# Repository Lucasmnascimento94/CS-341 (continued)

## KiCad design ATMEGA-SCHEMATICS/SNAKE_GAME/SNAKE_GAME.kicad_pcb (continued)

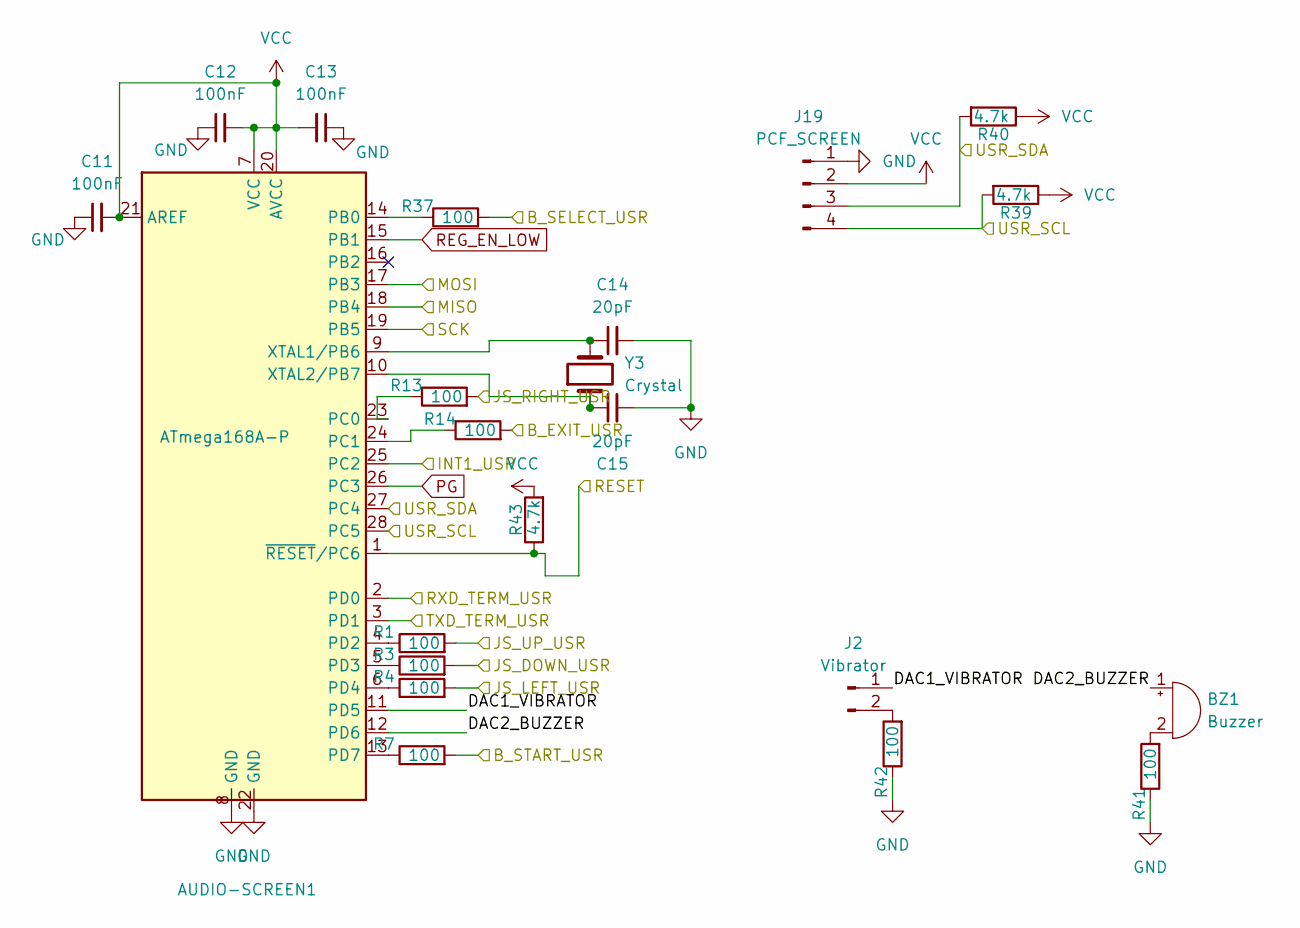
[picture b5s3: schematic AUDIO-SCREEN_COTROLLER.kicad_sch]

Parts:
AUDIO-SCREEN1: ATmega168A-P; DIP-28_W7.62mm
BZ1: Buzzer; Buzzer_12x9.5RM7.6
C11, C12, C13: 100nF; C_Disc_D7.5mm_W5.0mm_P5.00mm
C14, C15: 20pF; CP_Radial_D5.0mm_P2.50mm
J2: Vibrator; TerminalBlock_MaiXu_MX126-5.0-02P_1x02_P5.00mm
J19: PCF_SCREEN; TerminalBlock_MaiXu_MX126-5.0-04P_1x04_P5.00mm
R1, R3, R4, R7, R13, R14, R37, R41, R42: 100; R_Axial_DIN0207_L6.3mm_D2.5mm_P10.16mm_Horizontal
R39, R40, R43: 4.7k; R_Axial_DIN0207_L6.3mm_D2.5mm_P10.16mm_Horizontal
Y3: Crystal; Resonator-2Pin_W6.0mm_H3.0mm

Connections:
/AUDIO-SCREEN_CONTROLLER/B_EXIT_USR: R14.2; also elsewhere on the board
/AUDIO-SCREEN_CONTROLLER/B_SELECT_USR: R37.2; also elsewhere on the board
/AUDIO-SCREEN_CONTROLLER/B_START_USR: R7.2; also elsewhere on the board
/AUDIO-SCREEN_CONTROLLER/DAC1_VIBRATOR: AUDIO-SCREEN1.11 (PD5), J2.1
/AUDIO-SCREEN_CONTROLLER/DAC2_BUZZER: AUDIO-SCREEN1.12 (PD6), BZ1.1 (+)
/AUDIO-SCREEN_CONTROLLER/INT1_USR: AUDIO-SCREEN1.25 (PC2); also elsewhere on the board
/AUDIO-SCREEN_CONTROLLER/JS_DOWN_USR: R3.2; also elsewhere on the board
/AUDIO-SCREEN_CONTROLLER/JS_LEFT_USR: R4.2; also elsewhere on the board
/AUDIO-SCREEN_CONTROLLER/JS_RIGHT_USR: R13.2; also elsewhere on the board
/AUDIO-SCREEN_CONTROLLER/JS_UP_USR: R1.2; also elsewhere on the board
/AUDIO-SCREEN_CONTROLLER/MISO: AUDIO-SCREEN1.18 (PB4); also elsewhere on the board
/AUDIO-SCREEN_CONTROLLER/MOSI: AUDIO-SCREEN1.17 (PB3); also elsewhere on the board
/AUDIO-SCREEN_CONTROLLER/RESET: AUDIO-SCREEN1.1 (~RESET/PC6), R43.1; also elsewhere on the board
/AUDIO-SCREEN_CONTROLLER/RXD_TERM_USR: AUDIO-SCREEN1.2 (PD0); also elsewhere on the board
/AUDIO-SCREEN_CONTROLLER/SCK: AUDIO-SCREEN1.19 (PB5); also elsewhere on the board
/AUDIO-SCREEN_CONTROLLER/TXD_TERM_USR: AUDIO-SCREEN1.3 (PD1); also elsewhere on the board
/AUDIO-SCREEN_CONTROLLER/USR_SCL: AUDIO-SCREEN1.28 (PC5), J19.4, R39.2; also elsewhere on the board
/AUDIO-SCREEN_CONTROLLER/USR_SDA: AUDIO-SCREEN1.27 (PC4), J19.3, R40.2; also elsewhere on the board
GND: AUDIO-SCREEN1.8 (GND), AUDIO-SCREEN1.22 (GND), C11.1, C12.1, C13.1, C14.2, C15.2, J19.1, R41.1, R42.1; also elsewhere on the board
unnamed: AUDIO-SCREEN1.14 (PB0), R37.1
unnamed: AUDIO-SCREEN1.23 (PC0), R13.1
unnamed: AUDIO-SCREEN1.24 (PC1), R14.1
unnamed: AUDIO-SCREEN1.4 (PD2), R1.1
unnamed: AUDIO-SCREEN1.5 (PD3), R3.1
unnamed: AUDIO-SCREEN1.6 (PD4), R4.1
unnamed: AUDIO-SCREEN1.13 (PD7), R7.1
unnamed: AUDIO-SCREEN1.9 (XTAL1/PB6), C14.1, Y3.2
unnamed: AUDIO-SCREEN1.10 (XTAL2/PB7), C15.1, Y3.1
unnamed: BZ1.2 (-), R41.2
unnamed: J2.2, R42.2
PG: AUDIO-SCREEN1.26 (PC3); also elsewhere on the board
REG_EN_LOW: AUDIO-SCREEN1.15 (PB1); also elsewhere on the board
VCC: AUDIO-SCREEN1.7 (VCC), AUDIO-SCREEN1.20 (AVCC), AUDIO-SCREEN1.21 (AREF), C11.2, C12.2, C13.2, J19.2, R39.1, R40.1, R43.2; also elsewhere on the board

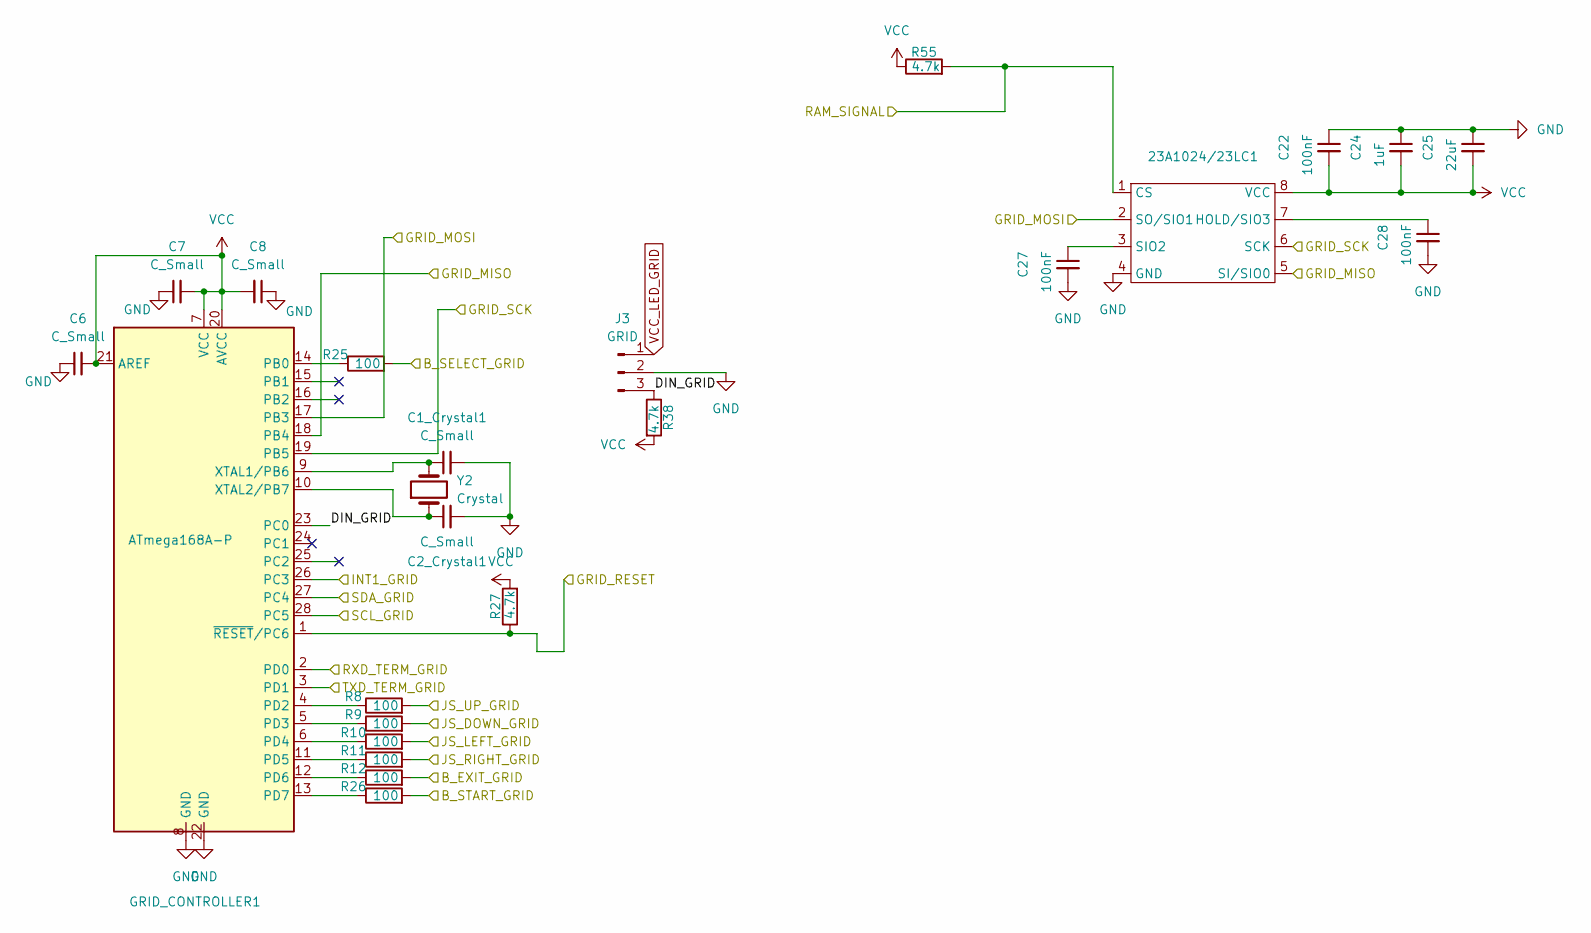
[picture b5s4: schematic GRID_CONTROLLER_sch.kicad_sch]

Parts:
23A1024/23LC1: CERDIP-8_W7.62mm_SideBrazed_Socket
C1_Crystal1, C2_Crystal1: C_Small; CP_Radial_D5.0mm_P2.50mm
C6, C7, C8: C_Small; C_Disc_D7.5mm_W5.0mm_P5.00mm
C22, C27, C28: 100nF; C_Disc_D7.5mm_W5.0mm_P5.00mm
C24: 1uF; C_Disc_D7.5mm_W5.0mm_P5.00mm
C25: 22uF; C_Disc_D7.5mm_W5.0mm_P5.00mm
GRID_CONTROLLER1: ATmega168A-P; DIP-28_W7.62mm
J3: GRID; TerminalBlock_MaiXu_MX126-5.0-03P_1x03_P5.00mm
R8, R9, R10, R11, R12, R25, R26: 100; R_Axial_DIN0207_L6.3mm_D2.5mm_P10.16mm_Horizontal
R27, R38, R55: 4.7k; R_Axial_DIN0207_L6.3mm_D2.5mm_P10.16mm_Horizontal
Y2: Crystal; Resonator-2Pin_W6.0mm_H3.0mm

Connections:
/AUDIO-SCREEN_CONTROLLER/B_EXIT_USR: R12.2; also elsewhere on the board
/AUDIO-SCREEN_CONTROLLER/B_SELECT_USR: R25.2; also elsewhere on the board
/AUDIO-SCREEN_CONTROLLER/B_START_USR: R26.2; also elsewhere on the board
/AUDIO-SCREEN_CONTROLLER/INT1_USR: GRID_CONTROLLER1.26 (PC3); also elsewhere on the board
/AUDIO-SCREEN_CONTROLLER/JS_DOWN_USR: R9.2; also elsewhere on the board
/AUDIO-SCREEN_CONTROLLER/JS_LEFT_USR: R10.2; also elsewhere on the board
/AUDIO-SCREEN_CONTROLLER/JS_RIGHT_USR: R11.2; also elsewhere on the board
/AUDIO-SCREEN_CONTROLLER/JS_UP_USR: R8.2; also elsewhere on the board
/AUDIO-SCREEN_CONTROLLER/RXD_TERM_USR: GRID_CONTROLLER1.2 (PD0); also elsewhere on the board
/AUDIO-SCREEN_CONTROLLER/TXD_TERM_USR: GRID_CONTROLLER1.3 (PD1); also elsewhere on the board
/AUDIO-SCREEN_CONTROLLER/USR_SCL: GRID_CONTROLLER1.28 (PC5); also elsewhere on the board
/AUDIO-SCREEN_CONTROLLER/USR_SDA: GRID_CONTROLLER1.27 (PC4); also elsewhere on the board
/CONTROLLERS/GRID_RAM_SIGNAL: 23A1024/23LC1.1 (CS), R55.2; also elsewhere on the board
/CONTROLLERS/MISO_GRID: 23A1024/23LC1.5 (SI/SIO0), GRID_CONTROLLER1.18 (PB4); also elsewhere on the board
/CONTROLLERS/MOSI_GRID: 23A1024/23LC1.2 (SO/SIO1), GRID_CONTROLLER1.17 (PB3); also elsewhere on the board
/CONTROLLERS/RESET_GRID: GRID_CONTROLLER1.1 (~RESET/PC6), R27.1; also elsewhere on the board
/CONTROLLERS/SCK_GRID: 23A1024/23LC1.6 (SCK), GRID_CONTROLLER1.19 (PB5); also elsewhere on the board
/GRID_CONTROLLER/DIN_GRID: GRID_CONTROLLER1.23 (PC0), J3.3, R38.1
GND: 23A1024/23LC1.4 (GND), C1_Crystal1.2, C2_Crystal1.2, C6.1, C7.1, C8.1, C22.1, C24.1, C25.1, C27.2, C28.2, GRID_CONTROLLER1.8 (GND), GRID_CONTROLLER1.22 (GND), J3.2; also elsewhere on the board
unnamed: 23A1024/23LC1.7 (HOLD/SIO3), C28.1
unnamed: 23A1024/23LC1.3 (SIO2), C27.1
unnamed: GRID_CONTROLLER1.14 (PB0), R25.1
unnamed: GRID_CONTROLLER1.4 (PD2), R8.1
unnamed: GRID_CONTROLLER1.5 (PD3), R9.1
unnamed: GRID_CONTROLLER1.6 (PD4), R10.1
unnamed: GRID_CONTROLLER1.11 (PD5), R11.1
unnamed: GRID_CONTROLLER1.12 (PD6), R12.1
unnamed: GRID_CONTROLLER1.13 (PD7), R26.1
unnamed: C1_Crystal1.1, GRID_CONTROLLER1.9 (XTAL1/PB6), Y2.2
unnamed: C2_Crystal1.1, GRID_CONTROLLER1.10 (XTAL2/PB7), Y2.1
VCC: 23A1024/23LC1.8 (VCC), C6.2, C7.2, C8.2, C22.2, C24.2, C25.2, GRID_CONTROLLER1.7 (VCC), GRID_CONTROLLER1.20 (AVCC), GRID_CONTROLLER1.21 (AREF), R27.2, R38.2, R55.1; also elsewhere on the board
VCC_LED_GRID: J3.1; also elsewhere on the board

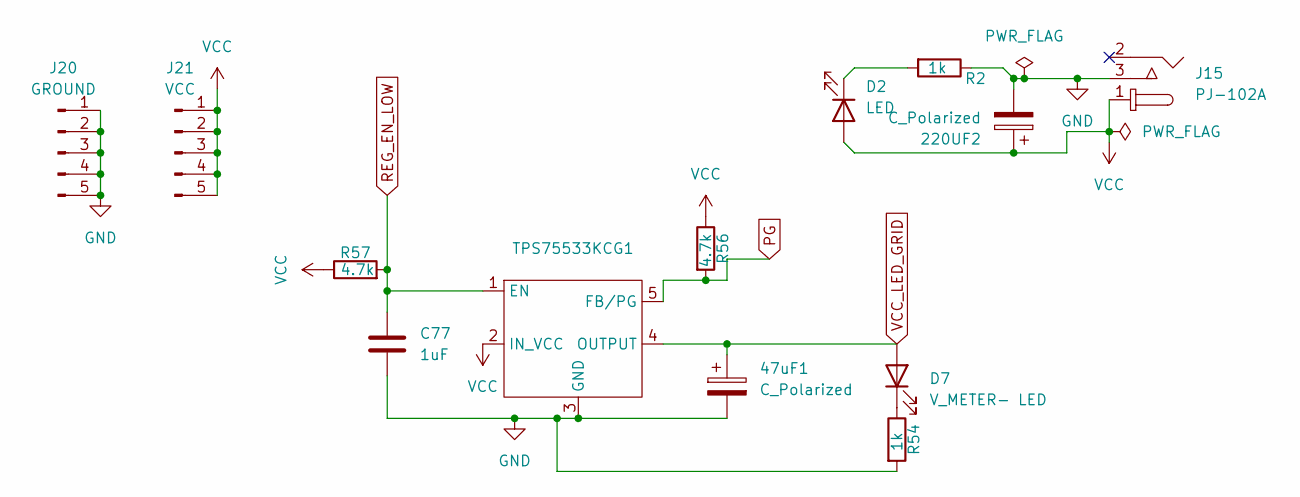
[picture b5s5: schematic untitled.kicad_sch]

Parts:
47uF1, 220UF2: C_Polarized; C_Disc_D3.0mm_W1.6mm_P2.50mm
C77: 1uF; C_Disc_D7.5mm_W5.0mm_P5.00mm
D2: LED; LED_D1.8mm_W3.3mm_H2.4mm
D7: V_METER- LED; LED_D1.8mm_W3.3mm_H2.4mm
J15: PJ-102A; BarrelJack_Horizontal; MPN PJ-102A; Digi-Key_PN CP-102A-ND
J20: GROUND; TerminalBlock_MaiXu_MX126-5.0-04P_1x04_P5.00mm
J21: VCC; TerminalBlock_MaiXu_MX126-5.0-04P_1x04_P5.00mm
R2, R54: 1k; R_Axial_DIN0207_L6.3mm_D2.5mm_P10.16mm_Horizontal
R56, R57: 4.7k; R_Axial_DIN0207_L6.3mm_D2.5mm_P10.16mm_Horizontal
TPS75533KCG1: TO-220-5_Vertical

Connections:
GND: 47uF1.2, 220UF2.2, C77.2, J15.3, J20.1, J20.2, J20.3, J20.4, J20.5, R2.1, R54.2, TPS75533KCG1.3 (GND); also elsewhere on the board
unnamed: D2.1 (K), R2.2
unnamed: D7.1 (K), R54.1
PG: R56.2, TPS75533KCG1.5 (FB/PG); also elsewhere on the board
REG_EN_LOW: C77.1, R57.2, TPS75533KCG1.1 (EN); also elsewhere on the board
VCC: 220UF2.1, D2.2 (A), J15.1, J21.1, J21.2, J21.3, J21.4, J21.5, R56.1, R57.1, TPS75533KCG1.2 (IN_VCC); also elsewhere on the board
VCC_LED_GRID: 47uF1.1, D7.2 (A), TPS75533KCG1.4 (OUTPUT); also elsewhere on the board

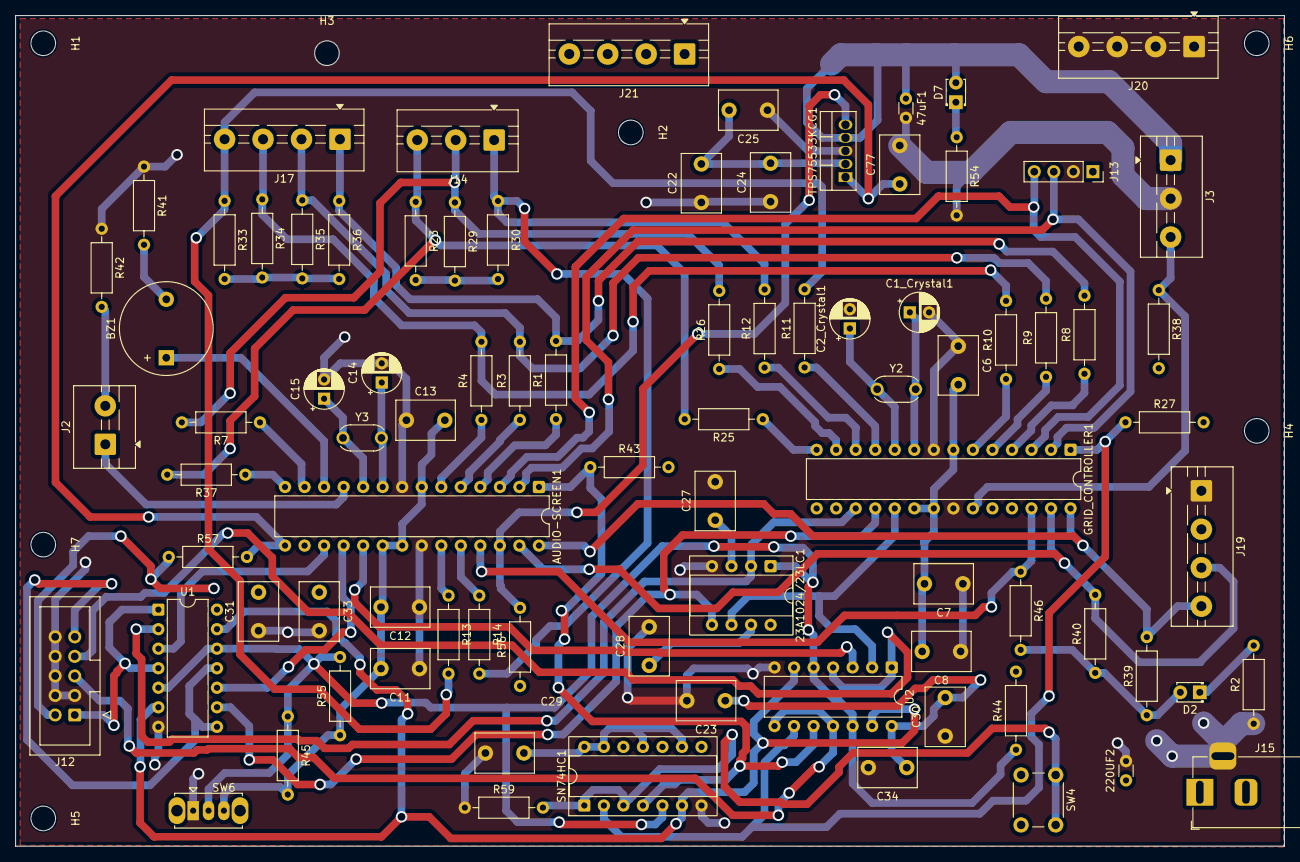
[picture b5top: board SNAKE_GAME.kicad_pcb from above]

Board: 2 copper layers, 165.0 x 108.0 mm, 92 parts (0 on the bottom side), 59 nets.

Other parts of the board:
C23: 100nF; C_Disc_D7.5mm_W5.0mm_P5.00mm
R44: 4.7k; R_Axial_DIN0207_L6.3mm_D2.5mm_P10.16mm_Horizontal

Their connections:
/CONTROLLERS/GRID_RAM_SIGNAL: R44.1; also elsewhere on the board
GND: C23.2; also elsewhere on the board
VCC: C23.1, R44.2; also elsewhere on the board

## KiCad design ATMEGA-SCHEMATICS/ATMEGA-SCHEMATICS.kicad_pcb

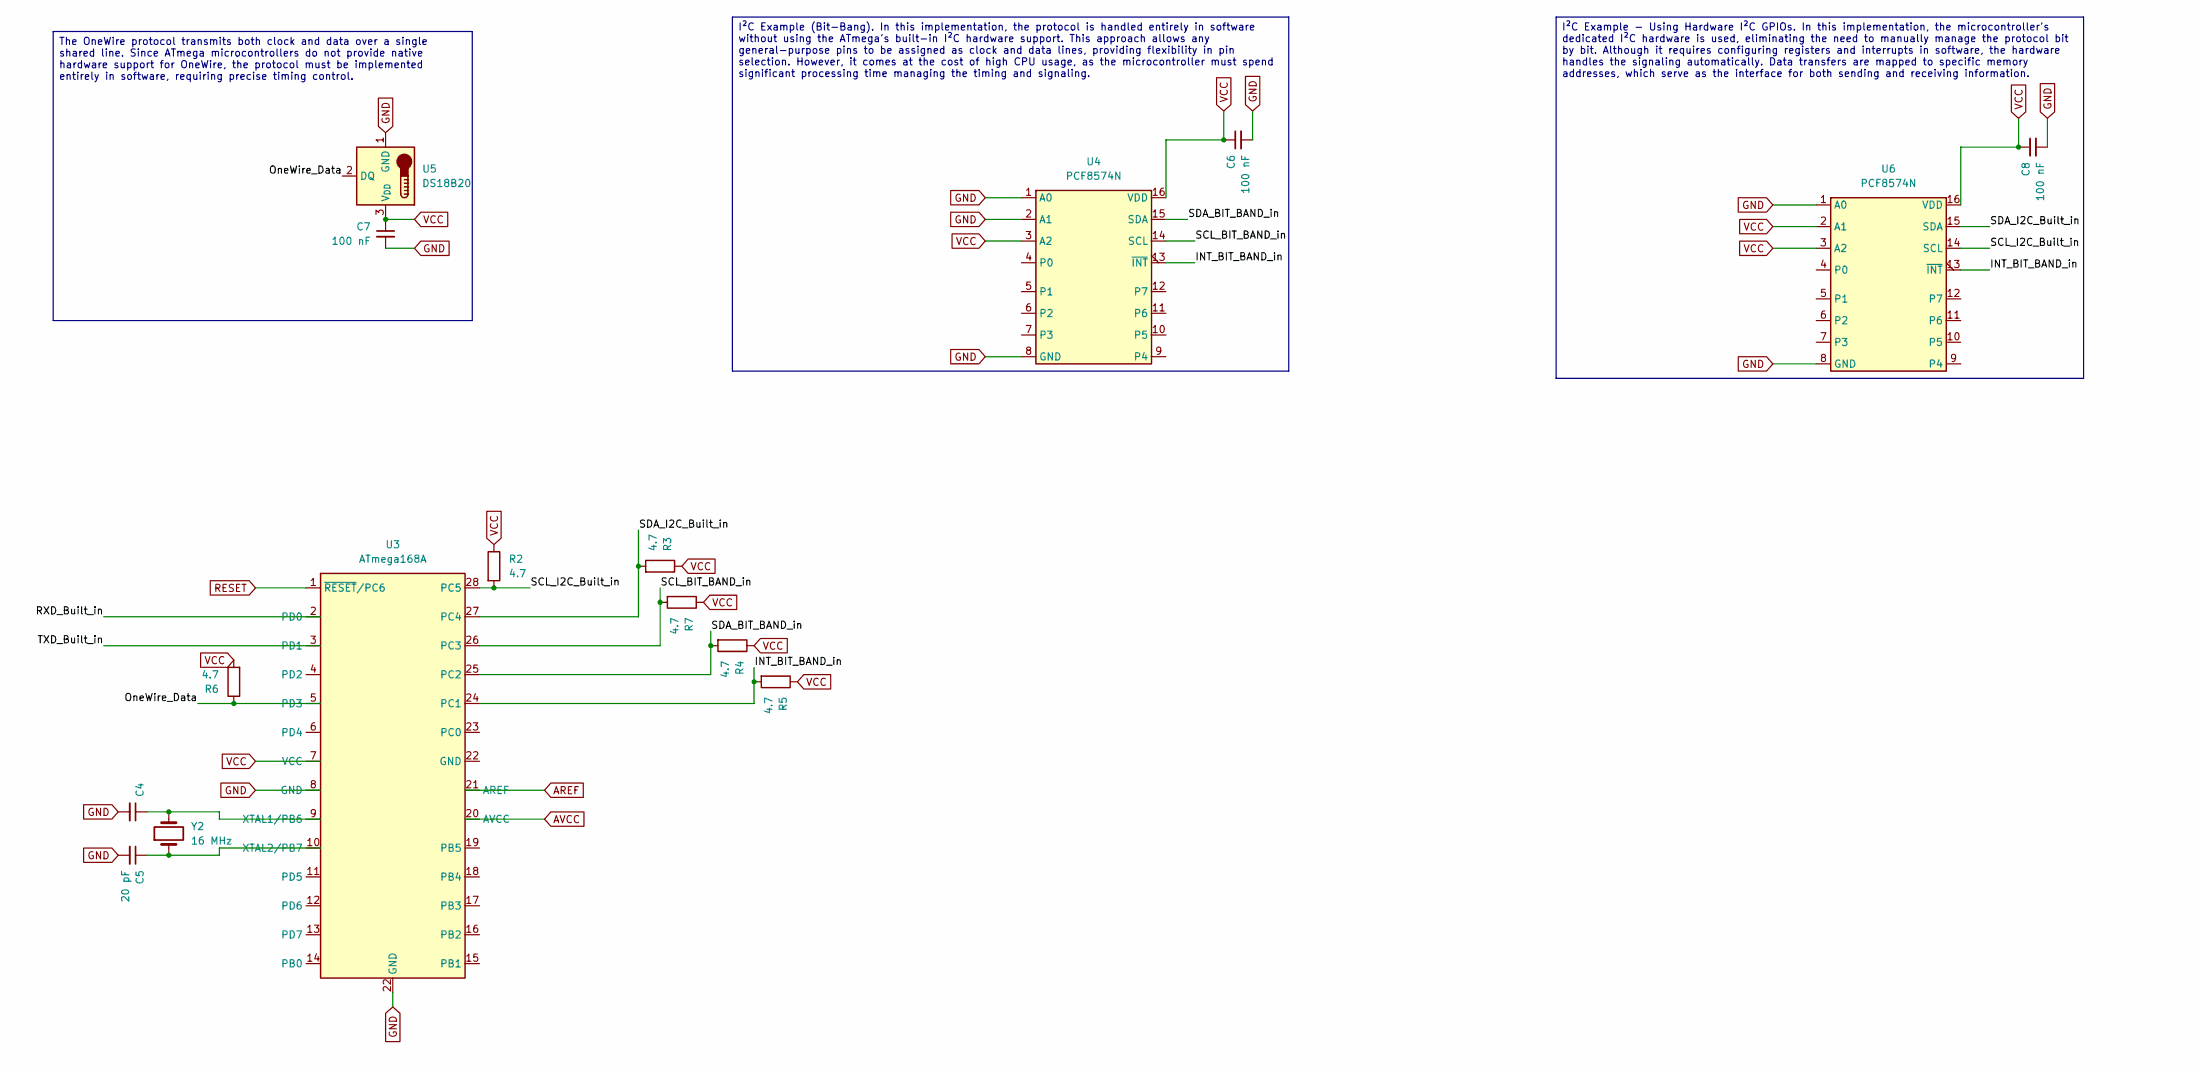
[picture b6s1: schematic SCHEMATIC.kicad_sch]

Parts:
C4, C5: 20 pF; CP_Radial_D5.0mm_P2.50mm
C6, C7, C8: 100 nF; CP_Radial_D5.0mm_P2.50mm
R2, R3, R4, R5, R6, R7: 4.7; R_Axial_DIN0207_L6.3mm_D2.5mm_P10.16mm_Horizontal
U3: ATmega168A; DIP-28_W7.62mm
U4, U6: PCF8574N; CERDIP-16_W7.62mm_SideBrazed_Socket
U5: DS18B20; TO-92_Inline
Y2: 16 MHz; Resonator-2Pin_W6.0mm_H3.0mm

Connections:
/SCHEMATIC_EXAMPLE/INT_BIT_BAND_in: R5.2, U3.24 (PC1), U4.13 (~INT), U6.13 (~INT)
/SCHEMATIC_EXAMPLE/OneWire_Data: R6.1, U3.5 (PD3), U5.2 (DQ)
/SCHEMATIC_EXAMPLE/RXD_Built_in: U3.2 (PD0)
/SCHEMATIC_EXAMPLE/SCL_BIT_BAND_in: R7.2, U3.26 (PC3), U4.14 (SCL)
/SCHEMATIC_EXAMPLE/SCL_I2C_Built_in: R2.2, U3.28 (PC5), U6.14 (SCL)
/SCHEMATIC_EXAMPLE/SDA_BIT_BAND_in: R4.2, U3.25 (PC2), U4.15 (SDA)
/SCHEMATIC_EXAMPLE/SDA_I2C_Built_in: R3.2, U3.27 (PC4), U6.15 (SDA)
/SCHEMATIC_EXAMPLE/TXD_Built_in: U3.3 (PD1)
AREF: U3.21 (AREF)
AVCC: U3.20 (AVCC)
GND: C4.2, C5.2, C6.2, C7.2, C8.2, U3.8 (GND), U3.22 (GND), U4.1 (A0), U4.2 (A1), U4.8 (GND), U5.1 (GND), U6.1 (A0), U6.8 (GND)
unnamed: C4.1, U3.9 (XTAL1/PB6), Y2.2
unnamed: C5.1, U3.10 (XTAL2/PB7), Y2.1
RESET: U3.1 (~RESET/PC6)
VCC: C6.1, C7.1, C8.1, R2.1, R3.1, R4.1, R5.1, R6.2, R7.1, U3.7 (VCC), U4.3 (A2), U4.16 (VDD), U5.3 (V_{DD}), U6.2 (A1), U6.3 (A2), U6.16 (VDD)

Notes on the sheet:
I²C Example - Using Hardware I²C GPIOs. In this implementation, the microcontroller's dedicated I²C hardware is used, eliminating the need to manually manage the protocol bit by bit. Although it requires configuring registers and interrupts in software, the hardware handles the signaling automatica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
The OneWire protocol transmits both clock and data over a single shared line. Since ATmega microcontrollers do not provide native hardware support for OneWire, the protocol must be implemented entirely in software, requiring precise timing control.
I²C Example (Bit-Bang). In this implementation, the protocol is handled entirely in software without using the ATmega's built-in I²C hardware support. This approach allows any general-purpose pins to be assigned as clock and data lines, providing flexibility in pin selection. However, it comes at t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

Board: 2 copper layers, 16 parts (0 on the bottom side), 10 nets, no tracks yet.

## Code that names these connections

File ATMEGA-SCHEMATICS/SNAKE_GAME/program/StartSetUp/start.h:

#ifndef START_H
#define START_H


#include "includes.h"

/*
JoyStick_UP    >> PD2 - PCINT18
JoyStick_DOWN  >> PD3 - PCINT19
JoyStick_LEFT  >> PD4 - PCINT20
JoyStick_RIGHT >> PD5 - PCINT21

*/

#define F_CPU 16000000UL

#define JOYSTICK_PORT PORTD
#define JOYSTICK_DDR DDRD
#define JOYSTICK_UP   PIN2
#define JOYSTICK_DOWN PIN3
#define JOYSTICK_LEFT PIN4
#define JOYSTICK_RIGHT PIN5

#define STALL   0x00
#define UP      0x01
#define DOWN    0x02
#define LEFT    0x03
#define RIGHT   0x04


#define LED_PORT PORTC
#define LED_DDR  DDRC
#define LED_PIN  PC0
#define GRID_PIXELS (48u*32u)


#define FOSC      16000000UL
#define BAUD_RATE 9600UL
#define MYUBRR    (FOSC/(16UL*BAUD_RATE) - 1) 

void gpioConfig();
void setUpISR();
void setUpUART();
void joyStickConf();

void seed_prng(void);

#endif

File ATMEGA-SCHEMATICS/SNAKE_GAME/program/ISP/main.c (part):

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    setUpUART();
    spiInit(&spi);

    DDRC |= (1<<PC1);
    PORTC |= (1<<PC1);
    targetSpiUpdate(&spi, &flash_conf);
    PORTD &= ~(1<<PD3);

    if(ispInit(&spi, &grid)){
        ispProgrammingEnable(&grid);
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
    cs_reg.CS_DDR = &SRAM_CS_DDR;
    cs_reg.CS_PORT = &SRAM_CS_PORT;
    cs_reg.CS_PIN = SRAM_CS_PIN;

    signal.SIGNAL_DDR = &SRAM_DDR;
    signal.SIGNAL_PORT = &SRAM_PORT;
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
    cs_reg.CS_DDR = &FLASH_CS_DDR;
    cs_reg.CS_PORT = &FLASH_CS_PORT;
    cs_reg.CS_PIN = FLASH_CS_PIN;

    signal.SIGNAL_DDR = &FLASH_DDR;
    signal.SIGNAL_PORT = &FLASH_PORT;
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
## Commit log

2025-09-22 recent
2025-10-01 SPI_application_note
2025-10-03 PWR_USBC_UART_ATMEGA8
    Come back to Earth - Mac Miller
2025-10-03 Code Update
    Update to main (previously 13 commits behind)
2025-10-04 Update to sram and main.c (grid_controller)
2025-10-04 sram and main.c changed in grid_controller
2025-10-04 edited schematics
2025-10-10 isp_tests initial commit
2025-10-10 removed spi .c .h
2025-10-10 updated comments + removed spi.h include
2025-10-13 testing writing blinky to target
2025-10-13 ispInit before ispPowerUp
2025-10-13 it works :)
2025-10-15 Converter_1
    Testing
2025-10-15 fixed CS toggling; timing delays follow avrdude/usbasp
2025-10-16 APA102 GRID DRIVER
    Initial APA102 driver header file & FPS Analysis.
2025-10-16 Pacman from Temu
    THIS IS A DEMO
2025-10-16 Spacecraft Simulator Demo.
2025-10-17 Reading
    Sources
2025-10-17 comments
2025-10-17 8MHz + flash readback "verification"
2025-10-17 cleaned up code + power test csvs for lucas
2025-10-17 off by one, also wrote the same page twice
2025-10-18 init MISO high; ispReadFuseByte; cleanup
2025-10-18 prog.
2025-10-21 Boutta KMS
    I WANT TO KMS SO MUCH
2025-10-21 converter
2025-10-21 328p
2025-10-22 Error
2025-10-22 Simple.c
    Write data to FT232RL
2025-10-22 Simple.c
    Correct version, bruv
2025-10-24 swapped args in ispLoadMemoryPage____Byte
2025-10-24 game
2025-10-24 ATmega8.c
    Initiate UART Protocol on ATmega8A
2025-11-03 Pacman
    Pacman Update
2025-11-04 converter init
2025-11-13 update 2
    changes to the map. to look like the original pacman added physics to walls.
    food consumptions animation and scoreboard.
2025-11-13 .
    Nothing much
2025-11-19 converter gitignore
2025-11-19 stm32-screen-test init
2025-11-19 minor fixes
2025-11-20 Icon for pac, pong, space
2025-11-21 all icons
2025-11-21 Updated doc
2025-11-25 .
    .
2025-11-25 Create snake_sim.py
    snake game simluations
2025-12-02 Testing
2025-12-02 Fixed V5
2025-12-02 fixed but not working
2025-12-08 Small Fix
2025-12-11 APA102 GRID API
    Embedded project SPI protocol and revisited mapping functions
